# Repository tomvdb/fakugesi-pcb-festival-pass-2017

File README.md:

# fakugesi-pcb-festival-pass-2017

Design files for fakugesi pcb festival pass 2017

# Make your own firmware

Processor: STM32F042

Compiler (free for stm32f0): http://www2.keil.com/stmicroelectronics-stm32/mdk

STM32 CubeMX file for code generation: firmware/fakugesi.ioc

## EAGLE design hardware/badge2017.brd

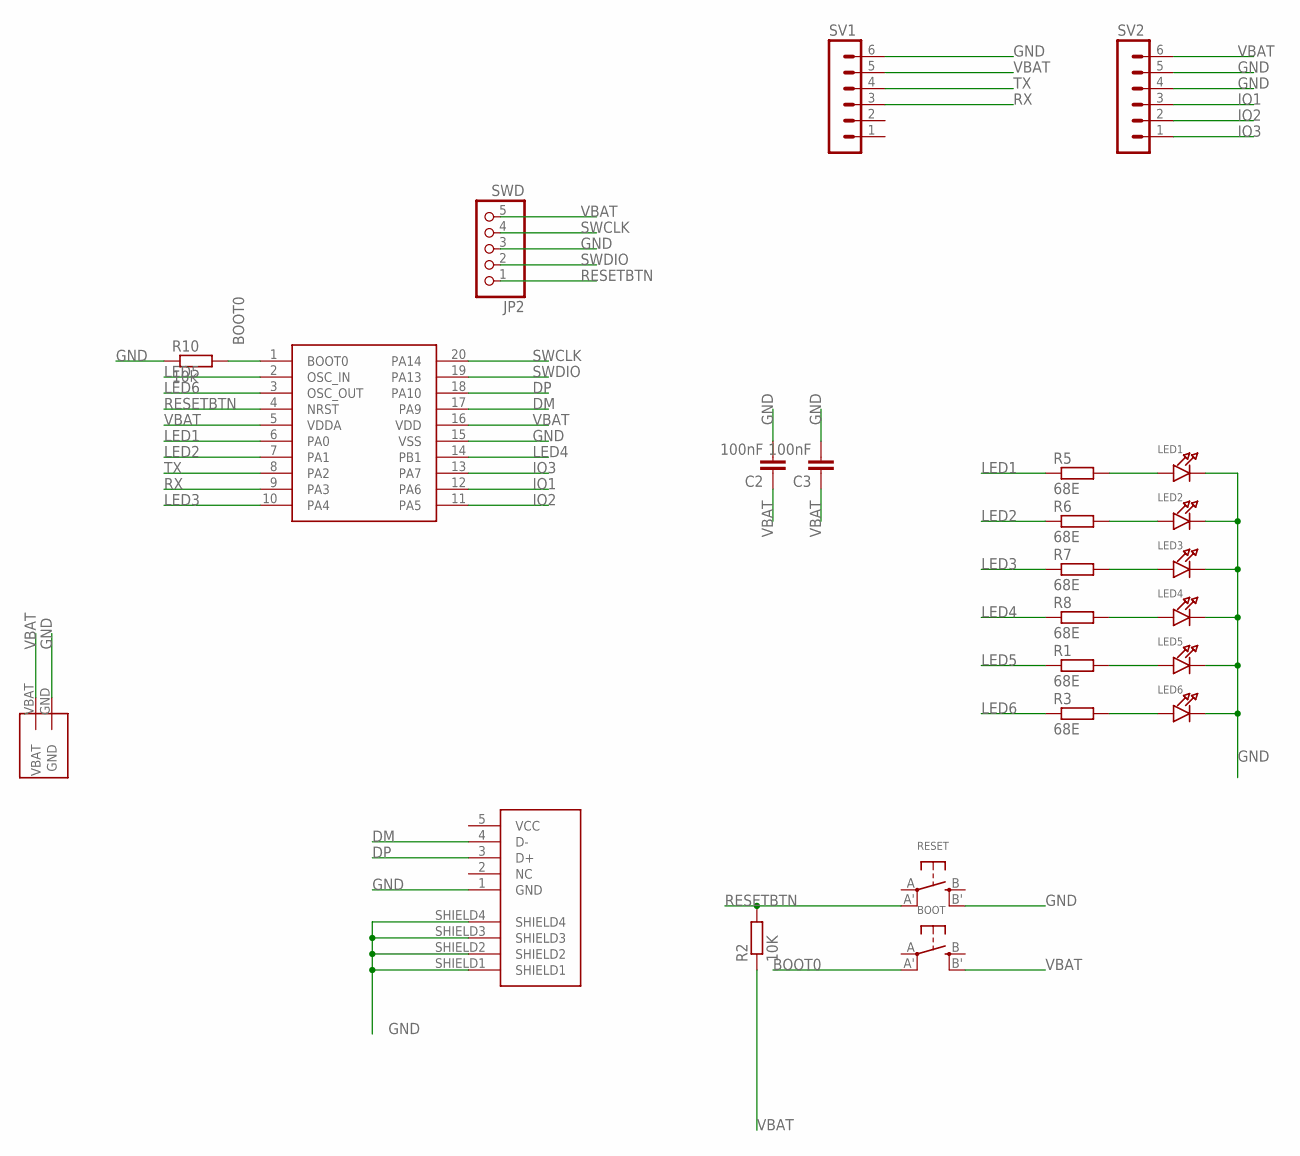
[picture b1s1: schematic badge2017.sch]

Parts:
BOOT: SWITCH_TACT_SMT; EVQ-Q2
C2, C3: 100nF; C0805
JP2: SWD; 1X05_OVAL
LED1, LED2, LED3, LED4, LED5, LED6: LED0805_NOOUTLINE; CHIPLED_0805_NOOUTLINE
R1, R3, R5, R6, R7, R8: 68E; R0805
R2: 10K; R0805
R10: 10k; R0805
RESET: SWITCH_TACT_SMT; EVQ-Q2
STM32: STM32F030X4792-5925; TSSOP20
SV1, SV2: MA06-1
U$1: 2AAPCBHOLDER; 2AAPCBBATTHOLDER
USB: USBSOCK_MINI_SMD

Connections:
BOOT0: BOOT.A' (P1), R10.2, STM32.1 (BOOT0)
DM: STM32.17 (PA9), USB.4 (D-)
DP: STM32.18 (PA10), USB.3 (D+)
GND: C2.2, C3.2, JP2.3, LED1.C, LED2.C, LED3.C, LED4.C, LED5.C, LED6.C, R10.1, RESET.B' (S1), STM32.15 (VSS), SV1.6, SV2.4, SV2.5, U$1.GND, USB.1 (GND), USB.SHIELD1, USB.SHIELD2, USB.SHIELD3, USB.SHIELD4
IO1: STM32.12 (PA6), SV2.3
IO2: STM32.11 (PA5), SV2.2
IO3: STM32.13 (PA7), SV2.1
LED1: R5.1, STM32.6 (PA0)
LED2: R6.1, STM32.7 (PA1)
LED3: R7.1, STM32.10 (PA4)
LED4: R8.1, STM32.14 (PB1)
LED5: R1.1, STM32.2 (OSC_IN)
LED6: R3.1, STM32.3 (OSC_OUT)
unnamed: LED1.A, R5.2
unnamed: LED2.A, R6.2
unnamed: LED3.A, R7.2
unnamed: LED4.A, R8.2
unnamed: LED5.A, R1.2
unnamed: LED6.A, R3.2
RESETBTN: JP2.1, R2.2, RESET.A' (P1), STM32.4 (NRST)
RX: STM32.9 (PA3), SV1.3
SWCLK: JP2.4, STM32.20 (PA14)
SWDIO: JP2.2, STM32.19 (PA13)
TX: STM32.8 (PA2), SV1.4
VBAT: BOOT.B' (S1), C2.1, C3.1, JP2.5, R2.1, STM32.5 (VDDA), STM32.16 (VDD), SV1.5, SV2.6, U$1.VBAT

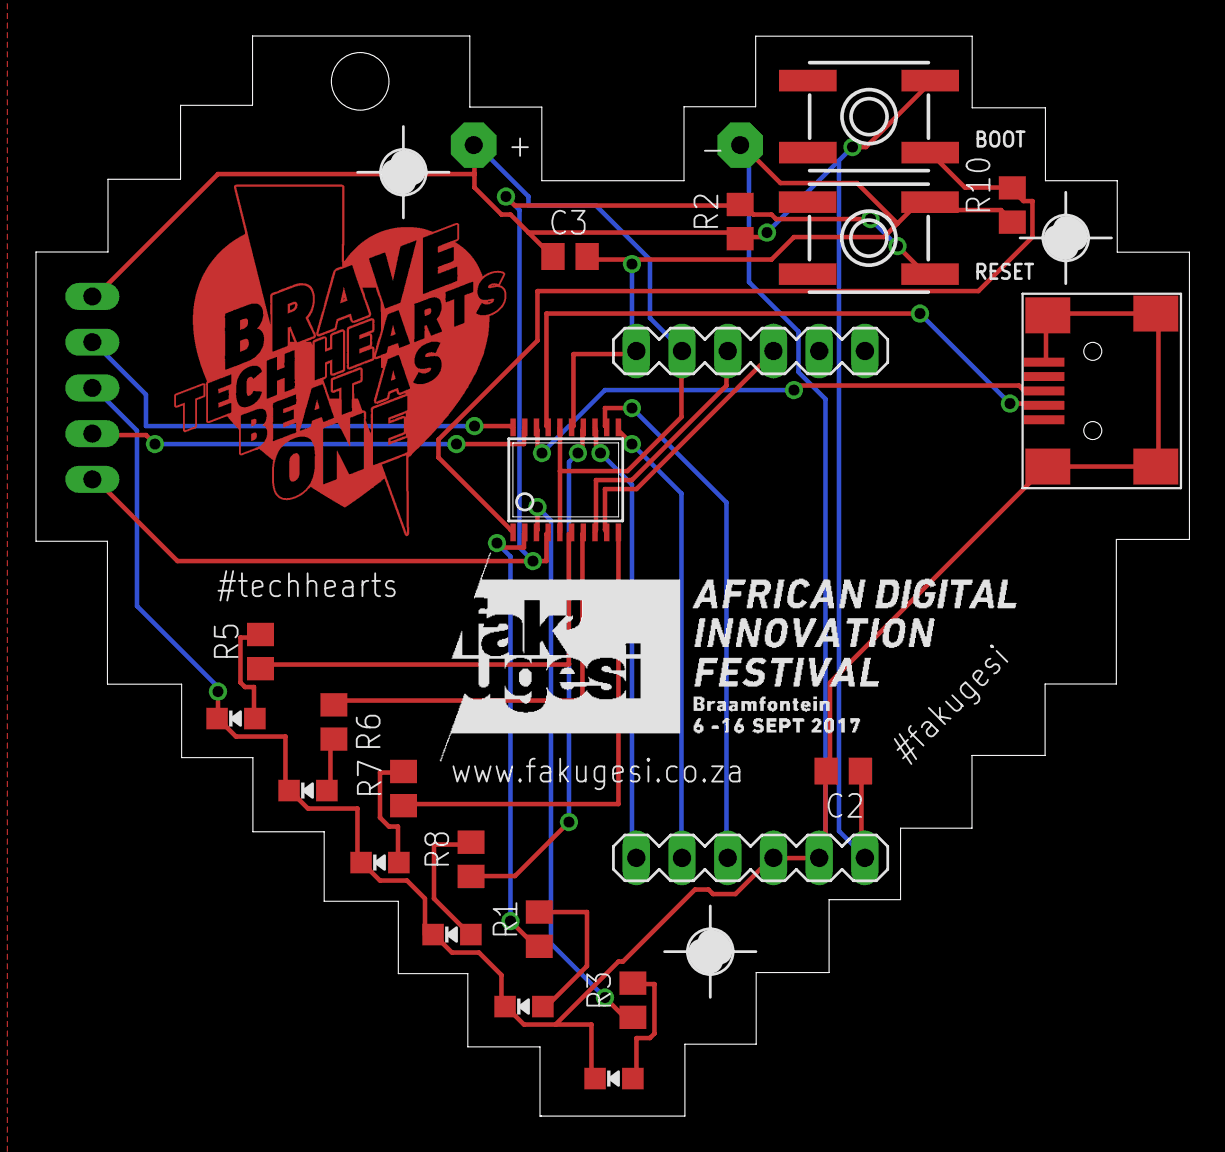
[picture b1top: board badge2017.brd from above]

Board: 2 copper layers, 64.1 x 60.0 mm, 27 parts (0 on the bottom side), 25 nets.

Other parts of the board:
U$2, U$3, U$4: PASS-ROUND

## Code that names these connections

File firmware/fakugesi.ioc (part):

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Mcu.Name=STM32F042F6Px
Mcu.Package=TSSOP20
Mcu.UserName=STM32F042F6Px
PA0.GPIOParameters=GPIO_Label
PA0.GPIO_Label=LED1
PA0.Signal=GPIO_Output
PA1.GPIOParameters=GPIO_Label
PA1.GPIO_Label=LED2
PA1.Signal=GPIO_Output
PA11.Mode=Device
PA11.Signal=USB_DM
PA12.Mode=Device
PA12.Signal=USB_DP
PA13.Mode=Serial_Wire
PA13.Signal=SYS_SWDIO
PA14.Mode=Serial_Wire
PA14.Signal=SYS_SWCLK
PA2.Mode=Asynchronous
PA2.Signal=USART2_TX
PA3.Mode=Asynchronous
PA3.Signal=USART2_RX
PA4.GPIOParameters=GPIO_Label
PA4.GPIO_Label=LED3
PA4.Signal=GPIO_Output
PA5.GPIOParameters=GPIO_Label
PA5.GPIO_Label=IO2
PA5.Signal=GPIO_Output
PA6.GPIOParameters=GPIO_Label
PA6.GPIO_Label=IO1
PA6.Signal=GPIO_Output
PA7.GPIOParameters=GPIO_Label
PA7.GPIO_Label=IO3
PA7.Signal=GPIO_Output
PB1.GPIOParameters=GPIO_Label
PB1.GPIO_Label=LED4
PB1.Signal=GPIO_Output
PB8.GPIOParameters=GPIO_Label
PB8.GPIO_Label=BUTTON
PB8.Signal=GPIO_Input
PF0-OSC_IN.GPIOParameters=GPIO_Label
PF0-OSC_IN.GPIO_Label=LED5
PF0-OSC_IN.Signal=GPIO_Output
PF1-OSC_OUT.GPIOParameters=GPIO_Label
PF1-OSC_OUT.GPIO_Label=LED6
PF1-OSC_OUT.Signal=GPIO_Output
RCC.SYSCLKFreq_VALUE=48000000
RCC.SYSCLKSource=RCC_SYSCLKSOURCE_HSI48

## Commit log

2017-09-06 fixed readme

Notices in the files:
parts and their libraries:
microbuilder: This work is placed in the public domain, and may be freely used for commercial and non-commercial work with the following conditions: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
